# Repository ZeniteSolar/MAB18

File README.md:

# MAB18
Módulo de Acionamento das Bombas 2018

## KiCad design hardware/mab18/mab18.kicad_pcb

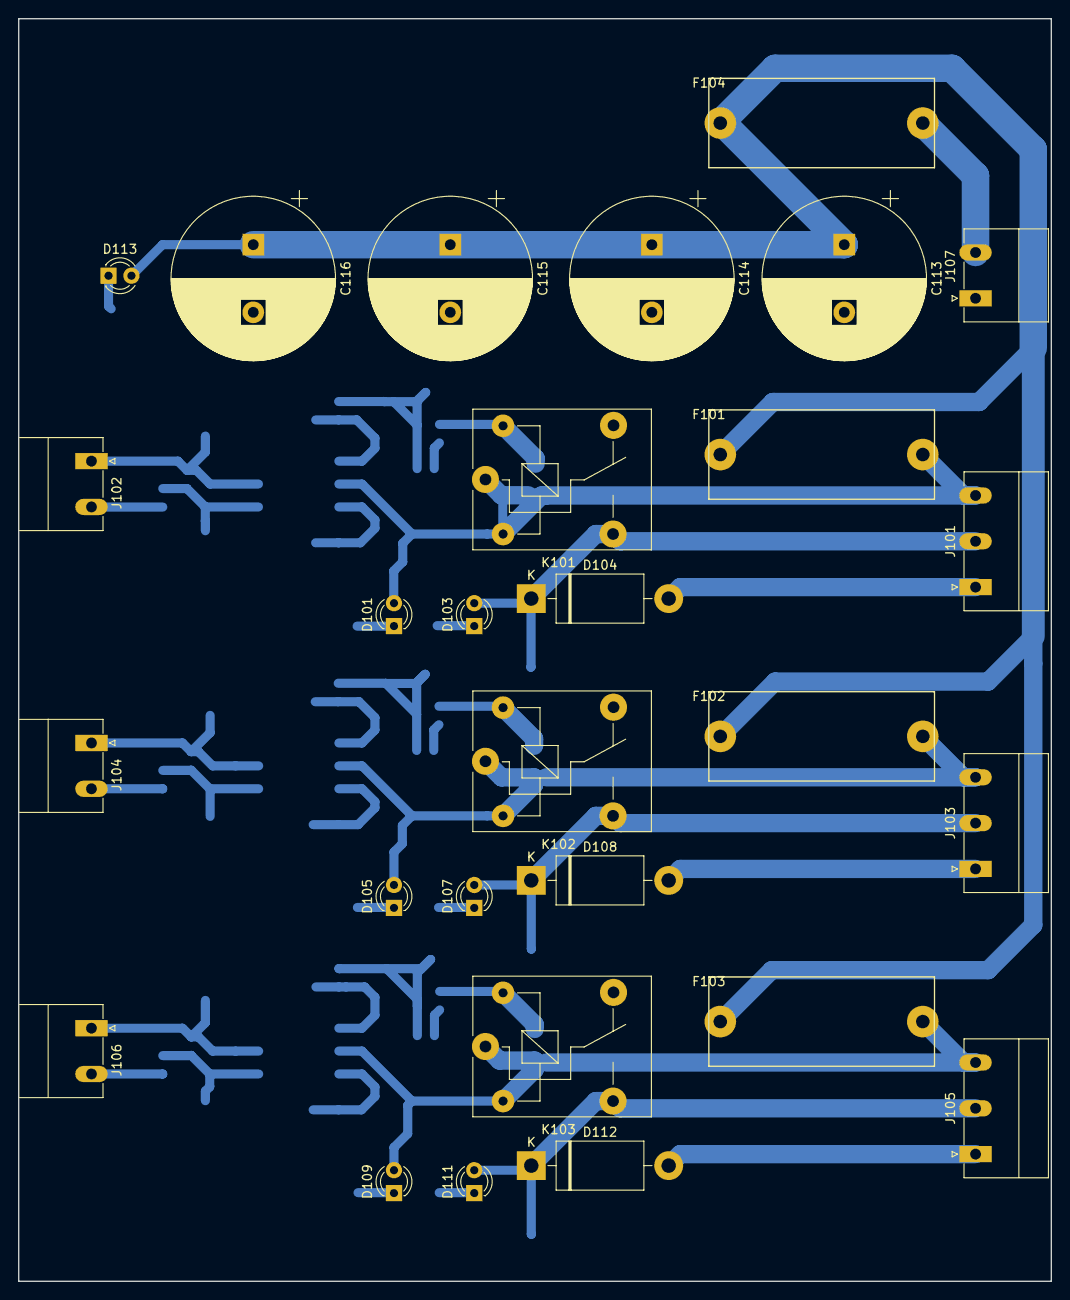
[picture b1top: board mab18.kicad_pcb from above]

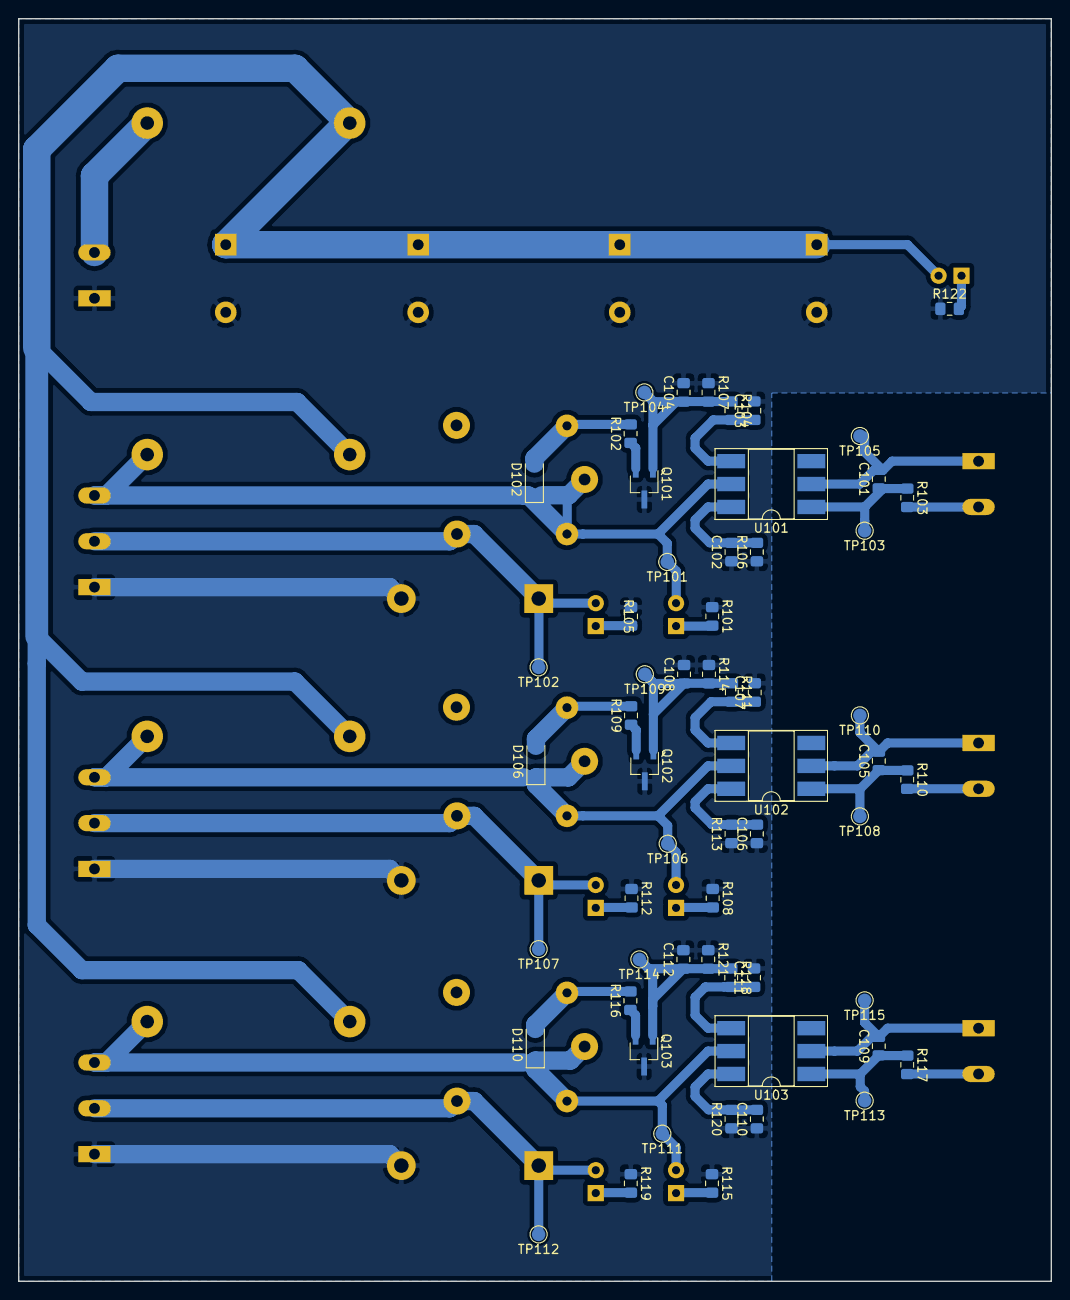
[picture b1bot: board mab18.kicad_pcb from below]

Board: 2 copper layers, 114.5 x 140.0 mm, 86 parts (58 on the bottom side), 40 nets.

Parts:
C101, C103, C104, C105, C107, C108, C109, C111, C112: 100n; C_0805_2012Metric_Pad1.15x1.40mm_HandSolder
C102, C106, C110: 1n; C_0805_2012Metric_Pad1.15x1.40mm_HandSolder
C113, C114, C115, C116: 4700u 35V; CP_Radial_D18.0mm_P7.50mm
D101, D105, D109, D113: G3mm; LED_D3.0mm
D102, D106, D110: LL4148; D_MiniMELF
D103, D107, D111: R3mm; LED_D3.0mm
D104, D108, D112: MUR460; D_DO-201AD_P15.24mm_Horizontal
F101, F102, F103: 3A; Fuse_Holder_5x20
F104: 10A; Fuse_Holder_5x20
J101, J103: PUMP_1 _OUT; PhoenixContact_MC_1,5_3-G-5.08_1x03_P5.08mm_Horizontal
J102: PUMP_1_IN; PhoenixContact_MC_1,5_2-G-5.08_1x02_P5.08mm_Horizontal
J104: PUMP_2_IN; PhoenixContact_MC_1,5_2-G-5.08_1x02_P5.08mm_Horizontal
J105: PUMP_3_OUT; PhoenixContact_MC_1,5_3-G-5.08_1x03_P5.08mm_Horizontal
J106: PUMP_3_IN; PhoenixContact_MC_1,5_2-G-5.08_1x02_P5.08mm_Horizontal
J107: BATTERY; PhoenixContact_MC_1,5_2-G-5.08_1x02_P5.08mm_Horizontal
K101, K102, K103: coil: 12VDC, contact: 125V/10A; Relay_SPDT_SANYOU_SRD_Series_Form_C
Q101, Q102, Q103: BCV27; TSOT-23_HandSoldering
R101, R105, R108, R112, R115, R119, R122: 1k; R_0805_2012Metric_Pad1.15x1.40mm_HandSolder
R102, R109, R116: 120R; R_0805_2012Metric_Pad1.15x1.40mm_HandSolder
R103, R110, R117: 330R; R_0805_2012Metric_Pad1.15x1.40mm_HandSolder
R104, R111, R118: 1k2; R_0805_2012Metric_Pad1.15x1.40mm_HandSolder
R106, R113, R120: NC; R_0805_2012Metric_Pad1.15x1.40mm_HandSolder
R107, R114, R121: 10k; R_0805_2012Metric_Pad1.15x1.40mm_HandSolder
TP101, TP106, TP111: 12V; TestPoint_Pad_D1.5mm
TP102: OUT1; TestPoint_Pad_D1.5mm
TP103: A1; TestPoint_Pad_D1.5mm
TP104: B1; TestPoint_Pad_D1.5mm
TP105: K1; TestPoint_Pad_D1.5mm
TP107: OUT2; TestPoint_Pad_D1.5mm
TP108: A2; TestPoint_Pad_D1.5mm
TP109: B2; TestPoint_Pad_D1.5mm
TP110: K2; TestPoint_Pad_D1.5mm
TP112: OUT3; TestPoint_Pad_D1.5mm
TP113: A3; TestPoint_Pad_D1.5mm
TP114: B3; TestPoint_Pad_D1.5mm
TP115: K3; TestPoint_Pad_D1.5mm
U101, U102, U103: 4N25; DIP-6_W8.89mm_SMDSocket_LongPads

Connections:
+12V: C113.1, C114.1, C115.1, C116.1, D113.2, F101.1, F102.1, F103.1, F104.1
GNDPWR: C102.1, C103.2, C104.2, C106.1, C107.2, C108.2, C110.1, C111.2, C112.2, C113.2, C114.2, C115.2, C116.2, D104.2, D108.2, D112.2, J101.1, J103.1, J105.1, J107.1, Q101.3, Q102.3, Q103.3, R101.1, R105.1, R106.1, R107.1, R108.1, R112.1, R113.1, R114.1, R115.1, R119.1, R120.1, R121.1, R122.1
unnamed: C101.1, R103.1, TP103.1, U101.1
unnamed: C101.2, J102.1, TP105.1, U101.2
unnamed: C102.2, R106.2, U101.6
unnamed: C103.1, R104.2, U101.4
unnamed: C104.1, Q101.1, R104.1, R107.2, TP104.1
unnamed: C105.1, R110.1, TP108.1, U102.1
unnamed: C105.2, J104.1, TP110.1, U102.2
unnamed: C106.2, R113.2, U102.6
unnamed: C107.1, R111.2, U102.4
unnamed: C108.1, Q102.1, R111.1, R114.2, TP109.1
unnamed: C109.1, R117.1, TP113.1, U103.1
unnamed: C109.2, J106.1, TP115.1, U103.2
unnamed: C110.2, R120.2, U103.6
unnamed: C111.1, R118.2, U103.4
unnamed: C112.1, Q103.1, R118.1, R121.2, TP114.1
unnamed: D101.1, R101.2
unnamed: D101.2, D102.1, F101.2, J101.3, K101.1, K101.2, TP101.1, U101.5
unnamed: D102.2, K101.5, R102.2
unnamed: D103.1, R105.2
unnamed: D103.2, D104.1, J101.2, K101.3, TP102.1
unnamed: D105.1, R108.2
unnamed: D105.2, D106.1, F102.2, J103.3, K102.1, K102.2, TP106.1, U102.5
unnamed: D106.2, K102.5, R109.2
unnamed: D107.1, R112.2
unnamed: D107.2, D108.1, J103.2, K102.3, TP107.1
unnamed: D109.1, R115.2
unnamed: D109.2, D110.1, F103.2, J105.3, K103.1, K103.2, TP111.1, U103.5
unnamed: D110.2, K103.5, R116.2
unnamed: D111.1, R119.2
unnamed: D111.2, D112.1, J105.2, K103.3, TP112.1
unnamed: D113.1, R122.2
unnamed: F104.2, J107.2
unnamed: J102.2, R103.2
unnamed: J104.2, R110.2
unnamed: J106.2, R117.2
unnamed: Q101.2, R102.1
unnamed: Q102.2, R109.1
unnamed: Q103.2, R116.1

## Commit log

2018-08-07 Schematic and PCB for a non microcontrolled version done. Revision needed
2018-08-07 PCB Stack changed. PCB DRC OK.
